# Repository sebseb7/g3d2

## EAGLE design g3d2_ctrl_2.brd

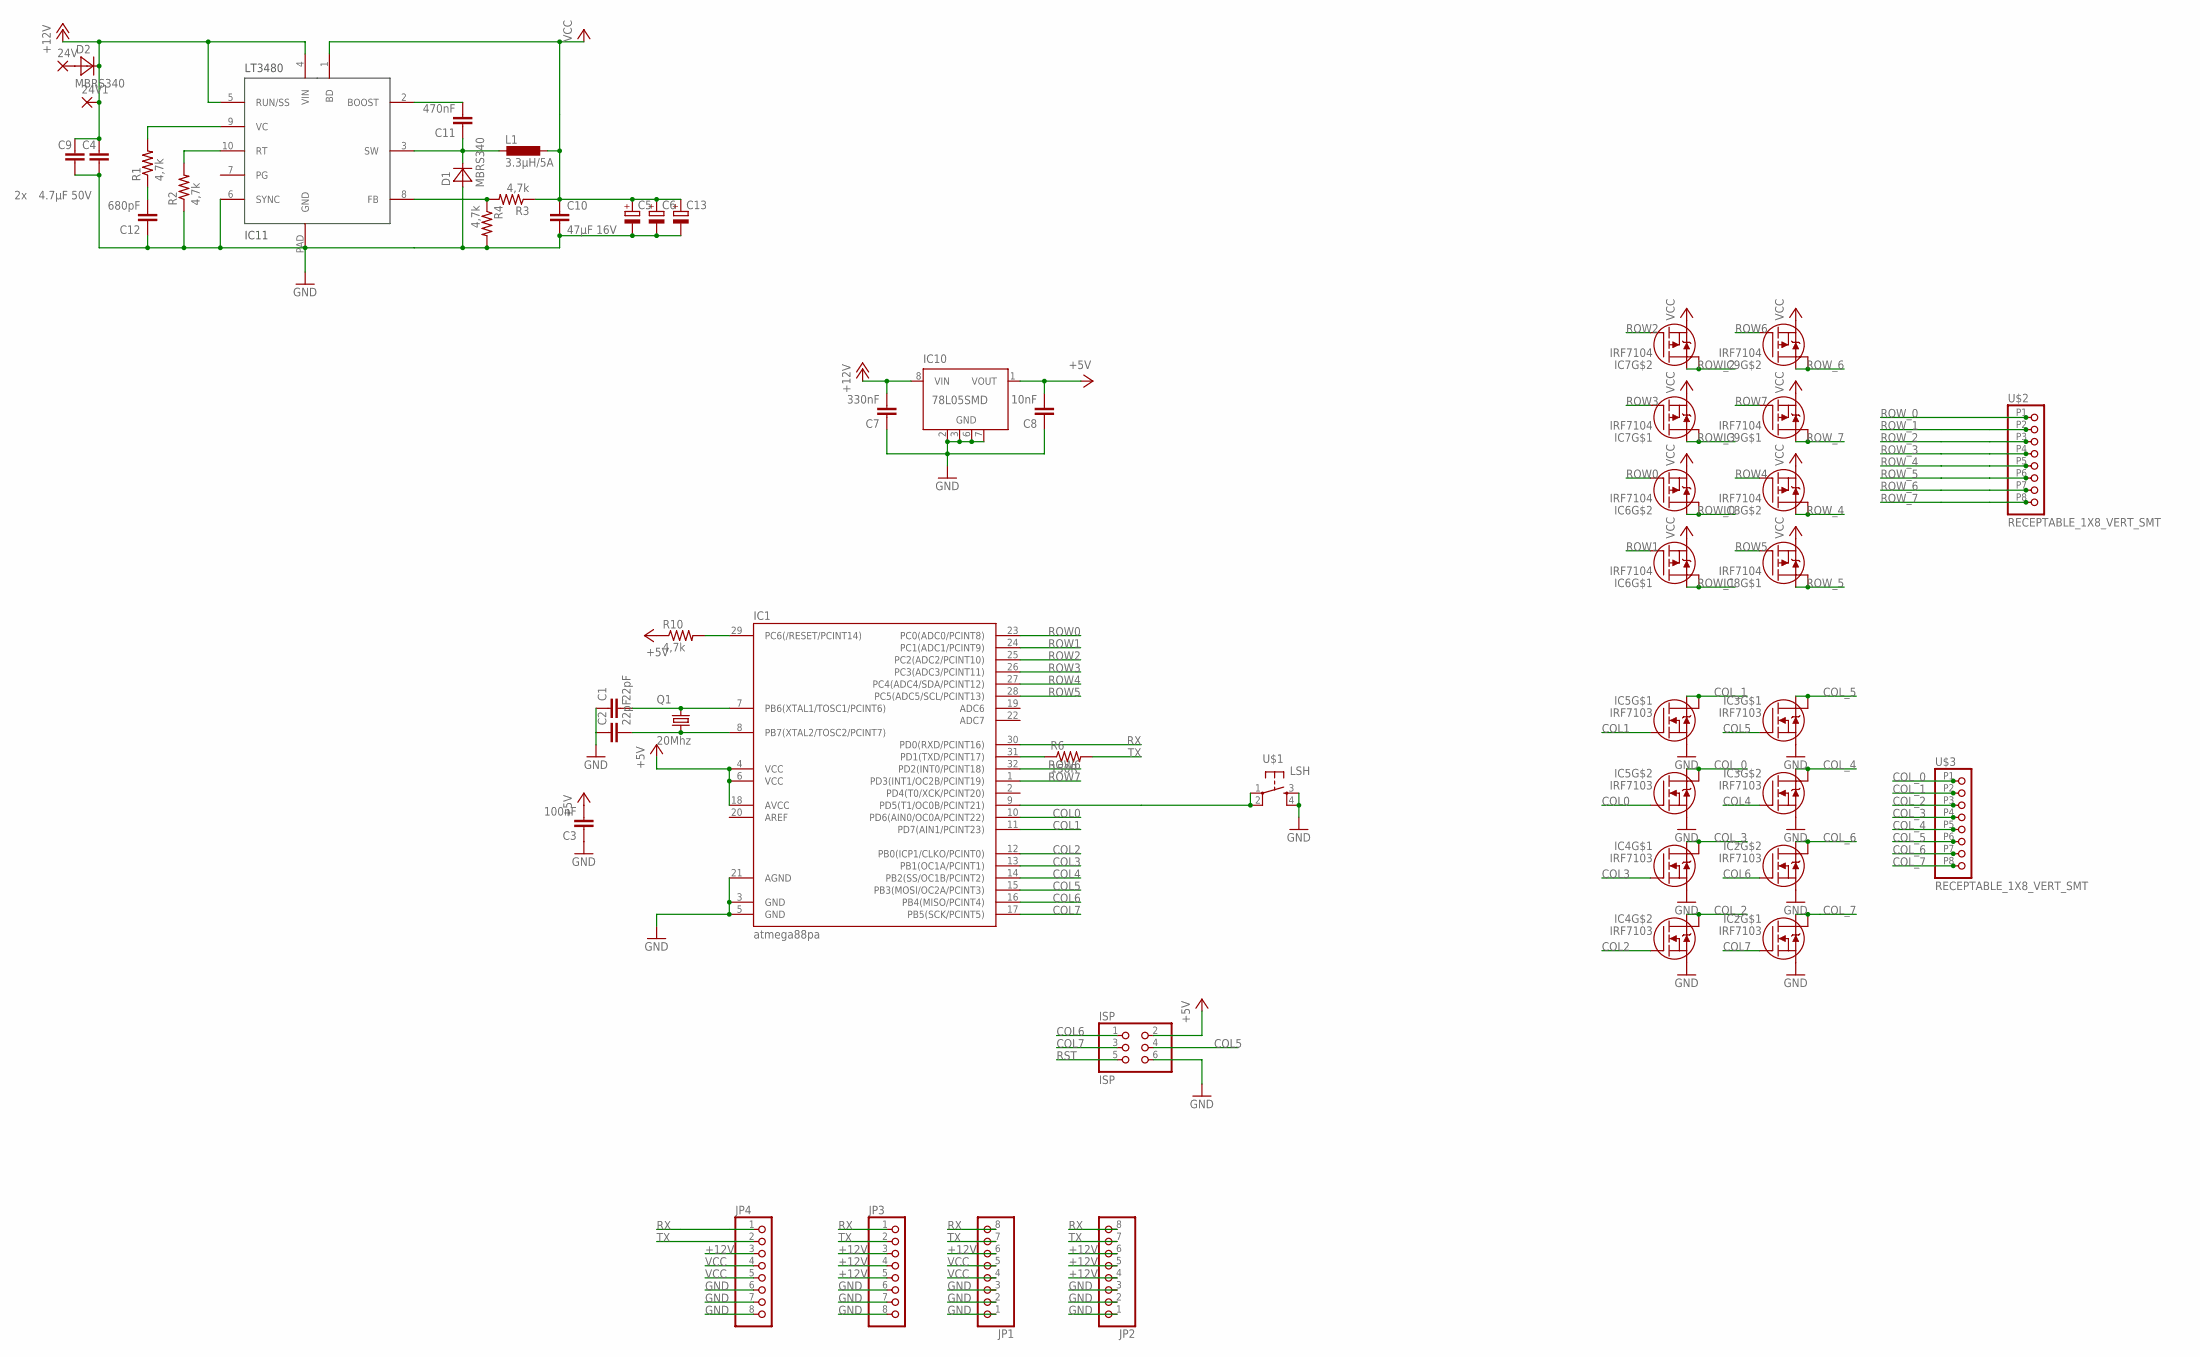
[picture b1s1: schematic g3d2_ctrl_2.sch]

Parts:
24V, 24V1: SMD5; SMD2,54-5,08
C1, C2: 22pF; 0805
C3: 100nF; 0805
C4, C9: 4.7µF 50V; 1210
C5, C6, C13: CPOL-EUSMCD; SMC_D
C7: 330nF; 0805
C8: 10nF; 0805
C10: 47µF 16V; 1210
C11: 470nF; 0805
C12: 680pF; 0805
D1, D2: MBRS340; DO214AB
IC1: atmega88pa; TQFP32-08
IC2, IC3, IC4, IC5: IRF7103; SO8-2
IC6, IC7, IC8, IC9: IRF7104; SO8-2
IC10: 78L05SMD; SO08
IC11: LT3972; MSOP10-PAD
ISP: ISP; 2X03
JP1, JP2, JP3, JP4: PINHD-1X08_2.54-SMD-90°; 1X08SMD/90
L1: 3.3µH/5A; DO3316P
Q1: 20Mhz; X22
R1, R2, R3, R4, R10: 4,7k; 0805
R6: 150R; 0805
U$1: LSH
U$2, U$3: RECEPTABLE_1X8_VERT_SMT

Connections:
+5V: C3.2, C8.2, IC1.4 (VCC), IC1.6 (VCC), IC1.18 (AVCC), IC10.1 (VOUT), ISP.2, R10.1
+12V: 24V1.1, C4.1, C7.2, C9.1, D2.K (C), IC10.8 (VIN), IC11.4 (VIN), IC11.5 (RUN/SS), JP1.6, JP2.4, JP2.5, JP2.6, JP3.3, JP3.4, JP3.5, JP4.3
COL0: IC1.10 (PD6(AIN0/OC0A/PCINT22)), IC5.4 (G)
COL1: IC1.11 (PD7(AIN1/PCINT23)), IC5.2 (G)
COL2: IC1.12 (PB0(ICP1/CLKO/PCINT0)), IC4.4 (G)
COL3: IC1.13 (PB1(OC1A/PCINT1)), IC4.2 (G)
COL4: IC1.14 (PB2(SS/OC1B/PCINT2)), IC3.4 (G)
COL5: IC1.15 (PB3(MOSI/OC2A/PCINT3)), IC3.2 (G), ISP.4
COL6: IC1.16 (PB4(MISO/PCINT4)), IC2.4 (G), ISP.1
COL7: IC1.17 (PB5(SCK/PCINT5)), IC2.2 (G), ISP.3
COL_0: IC5.5 (D), IC5.6 (D), U$3.P1 (1)
COL_1: IC5.7 (D), IC5.8 (D), U$3.P2 (2)
COL_2: IC4.5 (D), IC4.6 (D), U$3.P3 (3)
COL_3: IC4.7 (D), IC4.8 (D), U$3.P4 (4)
COL_4: IC3.5 (D), IC3.6 (D), U$3.P5 (5)
COL_5: IC3.7 (D), IC3.8 (D), U$3.P6 (6)
COL_6: IC2.5 (D), IC2.6 (D), U$3.P7 (7)
COL_7: IC2.7 (D), IC2.8 (D), U$3.P8 (8)
GND: C1.1, C2.1, C3.1, C4.2, C5.-, C6.-, C7.1, C8.1, C9.2, C10.2, C12.1, C13.-, D1.A, IC1.3 (GND), IC1.5 (GND), IC1.21 (AGND), IC2.1 (S), IC2.3 (S), IC3.1 (S), IC3.3 (S), IC4.1 (S), IC4.3 (S), IC5.1 (S), IC5.3 (S), IC10.2 (GND), IC10.3 (GND), IC10.6 (GND), IC10.7 (GND), IC11.6 (SYNC), IC11.PAD (GND), ISP.6, JP1.1, JP1.2, JP1.3, JP2.1, JP2.2, JP2.3, JP3.6, JP3.7, JP3.8, JP4.6, JP4.7, JP4.8, R2.1, R4.2, U$1.3, U$1.4
unnamed: C2.2, IC1.8 (PB7(XTAL2/TOSC2/PCINT7)), Q1.1
unnamed: C1.2, IC1.7 (PB6(XTAL1/TOSC1/PCINT6)), Q1.3 (2)
unnamed: IC1.31 (PD1(TXD/PCINT17)), R6.1
unnamed: 24V.1, D2.A
unnamed: IC11.10 (RT), R2.2
unnamed: IC1.9 (PD5(T1/OC0B/PCINT21)), U$1.1, U$1.2
unnamed: C12.2, R1.1
unnamed: IC11.9 (VC), R1.2
unnamed: C11.1, D1.K (C), IC11.3 (SW), L1.1
unnamed: IC11.8 (FB), R3.2, R4.1
unnamed: C11.2, IC11.2 (BOOST)
ROW0: IC1.23 (PC0(ADC0/PCINT8)), IC6.4 (G)
ROW1: IC1.24 (PC1(ADC1/PCINT9)), IC6.2 (G)
ROW2: IC1.25 (PC2(ADC2/PCINT10)), IC7.4 (G)
ROW3: IC1.26 (PC3(ADC3/PCINT11)), IC7.2 (G)
ROW4: IC1.27 (PC4(ADC4/SDA/PCINT12)), IC8.4 (G)
ROW5: IC1.28 (PC5(ADC5/SCL/PCINT13)), IC8.2 (G)
ROW6: IC1.32 (PD2(INT0/PCINT18)), IC9.4 (G)
ROW7: IC1.1 (PD3(INT1/OC2B/PCINT19)), IC9.2 (G)
ROW_0: IC6.5 (D), IC6.6 (D), U$2.P1 (1)
ROW_1: IC6.7 (D), IC6.8 (D), U$2.P2 (2)
ROW_2: IC7.5 (D), IC7.6 (D), U$2.P3 (3)
ROW_3: IC7.7 (D), IC7.8 (D), U$2.P4 (4)
ROW_4: IC8.5 (D), IC8.6 (D), U$2.P5 (5)
ROW_5: IC8.7 (D), IC8.8 (D), U$2.P6 (6)
ROW_6: IC9.5 (D), IC9.6 (D), U$2.P7 (7)
ROW_7: IC9.7 (D), IC9.8 (D), U$2.P8 (8)
RST: IC1.29 (PC6(/RESET/PCINT14)), ISP.5, R10.2
RX: IC1.30 (PD0(RXD/PCINT16)), JP1.8, JP2.8, JP3.1, JP4.1
TX: JP1.7, JP2.7, JP3.2, JP4.2, R6.2
VCC: C5.+, C6.+, C10.1, C13.+, IC6.1 (S), IC6.3 (S), IC7.1 (S), IC7.3 (S), IC8.1 (S), IC8.3 (S), IC9.1 (S), IC9.3 (S), IC11.1 (BD), JP1.4, JP1.5, JP4.4, JP4.5, L1.2, R3.1

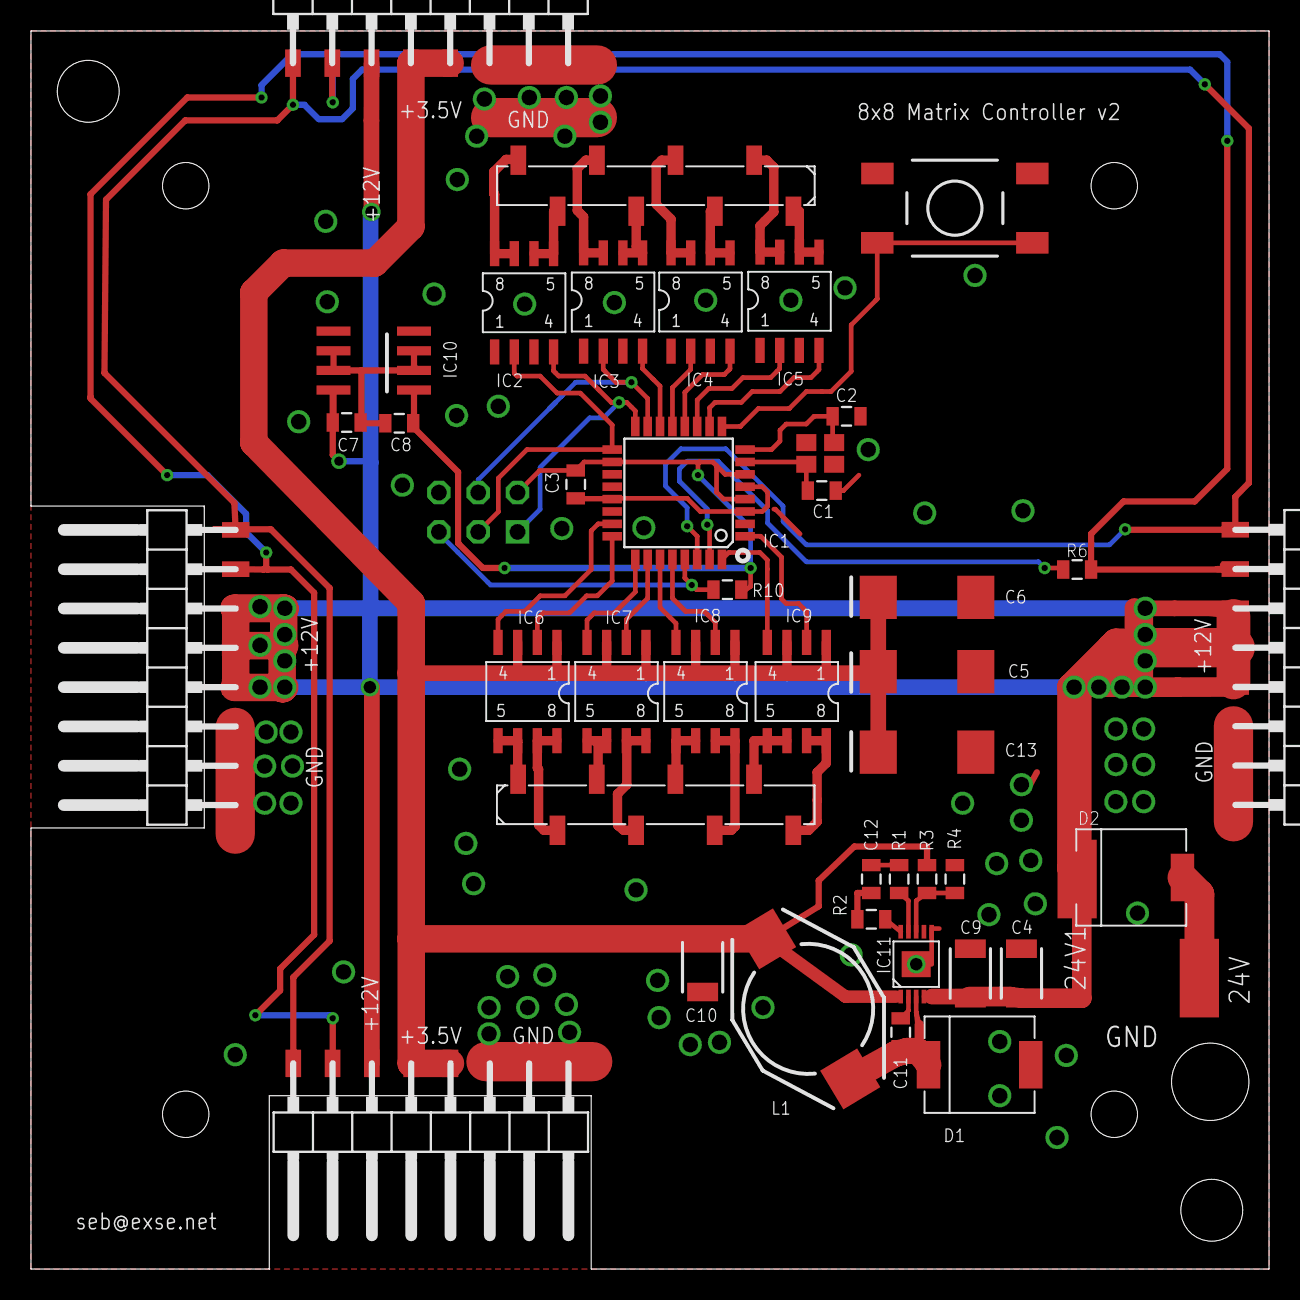
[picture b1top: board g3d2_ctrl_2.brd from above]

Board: 2 copper layers, 80.0 x 80.0 mm, 44 parts (1 on the bottom side), 50 nets.

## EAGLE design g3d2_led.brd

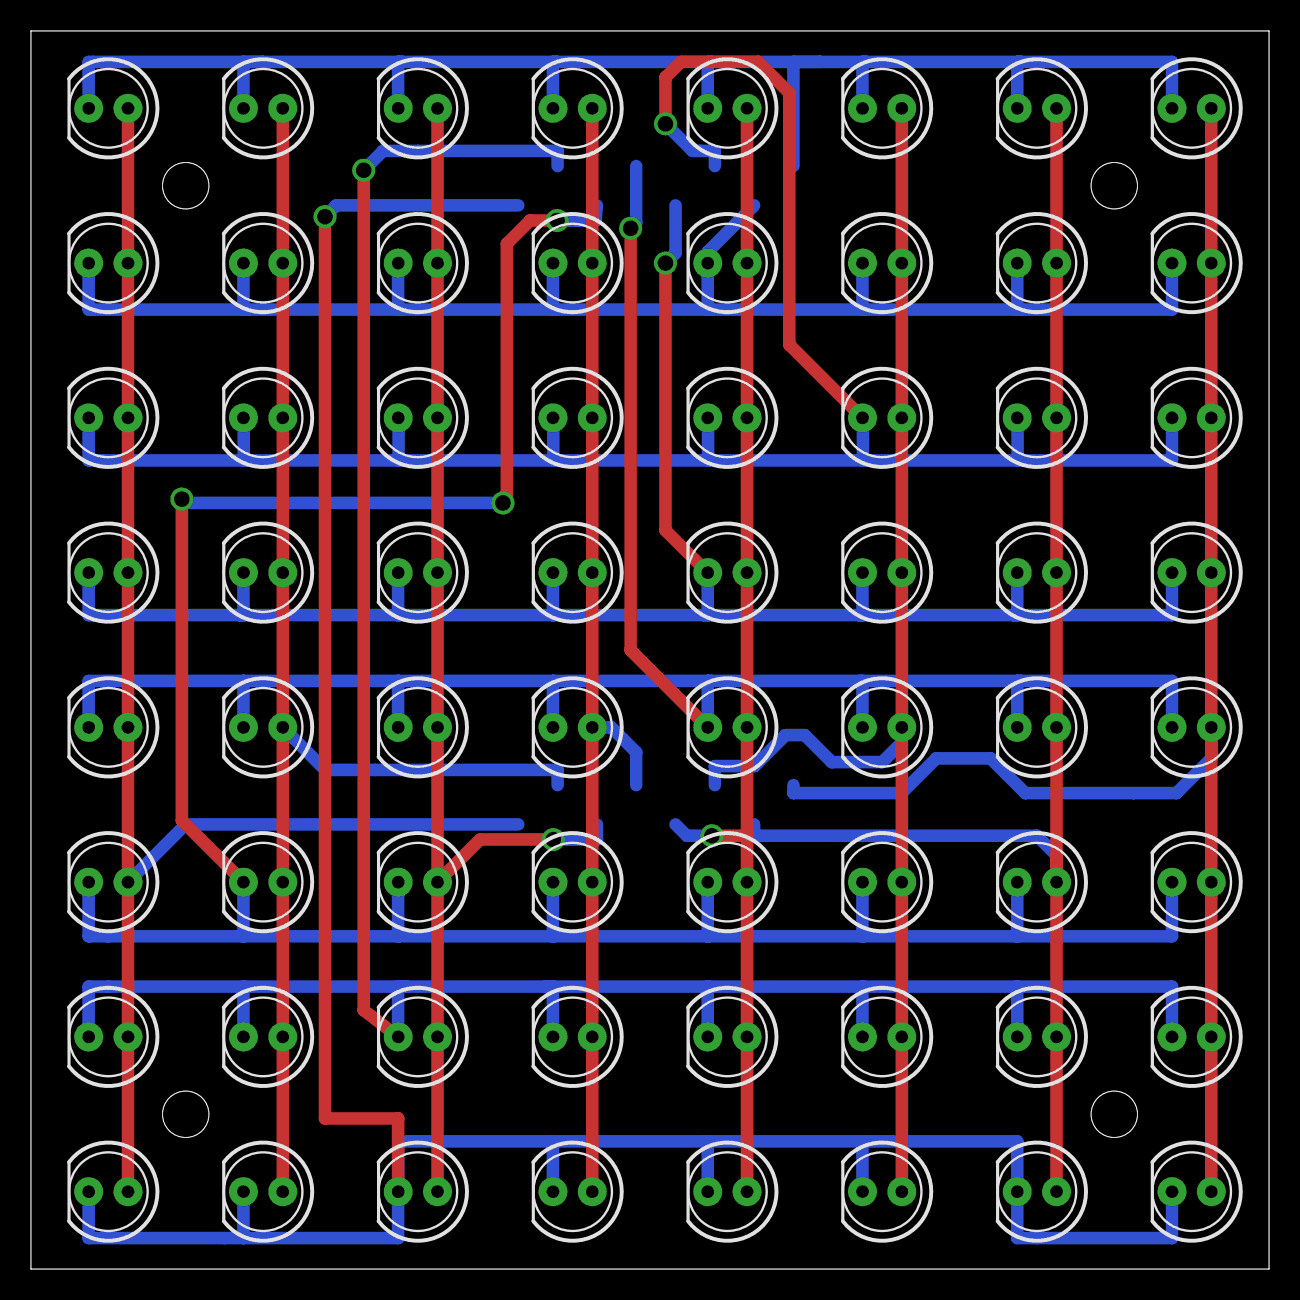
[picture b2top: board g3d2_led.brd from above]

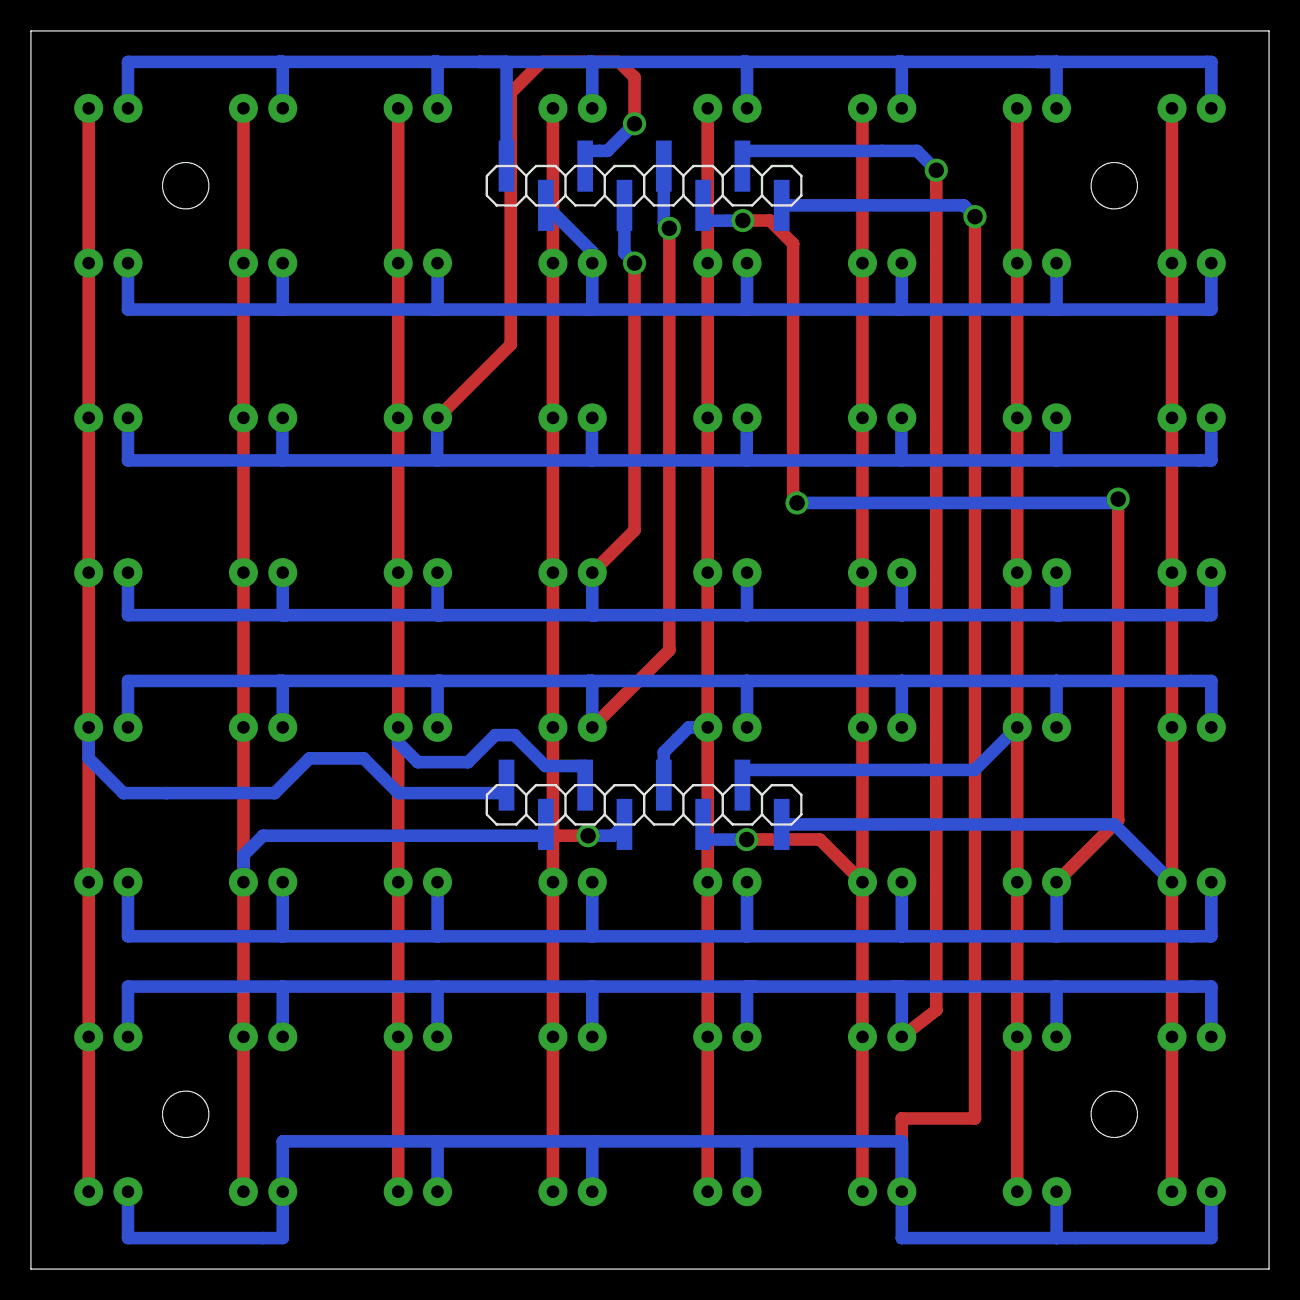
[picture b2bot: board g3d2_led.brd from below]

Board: 2 copper layers, 80.0 x 80.0 mm, 66 parts (2 on the bottom side), 16 nets.

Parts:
JP3, JP4: 1X08SMD
LED1, LED2, LED3, LED4, LED5, LED6, LED7, LED8, LED9, LED10, LED11, LED12, LED13, LED14, LED15, LED16, LED17, LED18, LED19, LED20, LED21, LED22, LED23, LED24, LED25, LED26, LED27, LED28, LED29, LED30, LED31, LED32, LED33, LED34, LED35, LED36, LED37, LED38, LED39, LED40, LED41, LED42, LED43, LED44, LED45, LED46, LED47, LED48, LED49, LED50, LED51, LED52, LED53, LED54, LED55, LED56, LED57, LED58, LED59, LED60, LED61, LED62, LED63, LED64: LED5MM

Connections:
unnamed: JP4.1, LED1.A, LED2.A, LED3.A, LED4.A, LED5.A, LED6.A, LED7.A, LED8.A
unnamed: JP4.2, LED9.A, LED10.A, LED11.A, LED12.A, LED13.A, LED14.A, LED15.A, LED16.A
unnamed: JP4.3, LED17.A, LED18.A, LED19.A, LED20.A, LED21.A, LED22.A, LED23.A, LED24.A
unnamed: JP4.4, LED25.A, LED26.A, LED27.A, LED28.A, LED29.A, LED30.A, LED31.A, LED32.A
unnamed: JP4.5, LED33.A, LED34.A, LED35.A, LED36.A, LED37.A, LED38.A, LED39.A, LED40.A
unnamed: JP4.6, LED41.A, LED42.A, LED43.A, LED44.A, LED45.A, LED46.A, LED47.A, LED48.A
unnamed: JP4.7, LED49.A, LED50.A, LED51.A, LED52.A, LED53.A, LED54.A, LED55.A, LED56.A
unnamed: JP4.8, LED57.A, LED58.A, LED59.A, LED60.A, LED61.A, LED62.A, LED63.A, LED64.A
unnamed: JP3.1, LED1.K, LED9.K, LED17.K, LED25.K, LED33.K, LED41.K, LED49.K, LED57.K
unnamed: JP3.2, LED2.K, LED10.K, LED18.K, LED26.K, LED34.K, LED42.K, LED50.K, LED58.K
unnamed: JP3.3, LED3.K, LED11.K, LED19.K, LED27.K, LED35.K, LED43.K, LED51.K, LED59.K
unnamed: JP3.4, LED4.K, LED12.K, LED20.K, LED28.K, LED36.K, LED44.K, LED52.K, LED60.K
unnamed: JP3.5, LED5.K, LED13.K, LED21.K, LED29.K, LED37.K, LED45.K, LED53.K, LED61.K
unnamed: JP3.6, LED6.K, LED14.K, LED22.K, LED30.K, LED38.K, LED46.K, LED54.K, LED62.K
unnamed: JP3.7, LED7.K, LED15.K, LED23.K, LED31.K, LED39.K, LED47.K, LED55.K, LED63.K
unnamed: JP3.8, LED8.K, LED16.K, LED24.K, LED32.K, LED40.K, LED48.K, LED56.K, LED64.K

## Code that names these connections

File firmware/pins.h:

#ifndef _PINS_H
#define _PINS_H


#define COL0_PORT PORTD
#define COL1_PORT PORTD
#define COL2_PORT PORTB
#define COL3_PORT PORTB
#define COL4_PORT PORTB
#define COL5_PORT PORTB
#define COL6_PORT PORTB
#define COL7_PORT PORTB

#define ROW0_PORT PORTC
#define ROW1_PORT PORTC
#define ROW2_PORT PORTC
#define ROW3_PORT PORTC
#define ROW4_PORT PORTC
#define ROW5_PORT PORTC
#define ROW6_PORT PORTD
#define ROW7_PORT PORTD

#define COL0_DDR DDRD
#define COL1_DDR DDRD
#define COL2_DDR DDRB
#define COL3_DDR DDRB
#define COL4_DDR DDRB
#define COL5_DDR DDRB
#define COL6_DDR DDRB
#define COL7_DDR DDRB

#define ROW0_DDR DDRC
#define ROW1_DDR DDRC
#define ROW2_DDR DDRC
#define ROW3_DDR DDRC
#define ROW4_DDR DDRC
#define ROW5_DDR DDRC
#define ROW6_DDR DDRD
#define ROW7_DDR DDRD

#define COL0_PIN PIND6
#define COL1_PIN PIND7
#define COL2_PIN PINB0
#define COL3_PIN PINB1
#define COL4_PIN PINB2
#define COL5_PIN PINB3
#define COL6_PIN PINB4
#define COL7_PIN PINB5

#define ROW0_PIN PINC0
#define ROW1_PIN PINC1
#define ROW2_PIN PINC2
#define ROW3_PIN PINC3
#define ROW4_PIN PINC4
#define ROW5_PIN PINC5
#define ROW6_PIN PIND2
#define ROW7_PIN PIND3

#define ROW0_OFF ROW0_PORT |= (1<<ROW0_PIN)
#define ROW1_OFF ROW1_PORT |= (1<<ROW1_PIN)
#define ROW2_OFF ROW2_PORT |= (1<<ROW2_PIN)
#define ROW3_OFF ROW3_PORT |= (1<<ROW3_PIN)
#define ROW4_OFF ROW4_PORT |= (1<<ROW4_PIN)
#define ROW5_OFF ROW5_PORT |= (1<<ROW5_PIN)
#define ROW6_OFF ROW6_PORT |= (1<<ROW6_PIN)
#define ROW7_OFF ROW7_PORT |= (1<<ROW7_PIN)

#define ROW0_ON ROW0_PORT &= ~(1<<ROW0_PIN)
#define ROW1_ON ROW1_PORT &= ~(1<<ROW1_PIN)
#define ROW2_ON ROW2_PORT &= ~(1<<ROW2_PIN)
#define ROW3_ON ROW3_PORT &= ~(1<<ROW3_PIN)
#define ROW4_ON ROW4_PORT &= ~(1<<ROW4_PIN)
#define ROW5_ON ROW5_PORT &= ~(1<<ROW5_PIN)
#define ROW6_ON ROW6_PORT &= ~(1<<ROW6_PIN)
#define ROW7_ON ROW7_PORT &= ~(1<<ROW7_PIN)

#define COL0_ON COL0_PORT |= (1<<COL0_PIN)
#define COL1_ON COL1_PORT |= (1<<COL1_PIN)
#define COL2_ON COL2_PORT |= (1<<COL2_PIN)
#define COL3_ON COL3_PORT |= (1<<COL3_PIN)
#define COL4_ON COL4_PORT |= (1<<COL4_PIN)
#define COL5_ON COL5_PORT |= (1<<COL5_PIN)
#define COL6_ON COL6_PORT |= (1<<COL6_PIN)
#define COL7_ON COL7_PORT |= (1<<COL7_PIN)

#define COL0_OFF COL0_PORT &= ~(1<<COL0_PIN)
#define COL1_OFF COL1_PORT &= ~(1<<COL1_PIN)
#define COL2_OFF COL2_PORT &= ~(1<<COL2_PIN)
#define COL3_OFF COL3_PORT &= ~(1<<COL3_PIN)
#define COL4_OFF COL4_PORT &= ~(1<<COL4_PIN)
#define COL5_OFF COL5_PORT &= ~(1<<COL5_PIN)
#define COL6_OFF COL6_PORT &= ~(1<<COL6_PIN)
#define COL7_OFF COL7_PORT &= ~(1<<COL7_PIN)


#endif

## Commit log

2011-10-28 initial
2011-10-28 2nd image
2011-11-04 moved to here
2011-11-04 new images
2011-11-04 another image added
2011-11-04 values added
2011-11-17 fixed collision
2011-11-17 fixed tnames fontsize
2011-11-17 fixed a few clearance problems
2011-11-20 initial test version (barebone) of g3d2 master firmware
2011-11-20 now binaries depend on the makefile
2011-11-20 small fixes
2011-11-20 -O0 > -O1 (binary nearly 50% smaller)
2011-11-20 added wildcards for .c and .s
2011-11-20 removed stuff
2011-11-21 moved path to bash_profile
2011-11-21 fixed line-breaks , added uart driver
2011-11-21 osx fix
2011-11-21 gitignore
2011-11-21 added some values
2011-11-21 case
2011-11-21 newer lpc headers, removed unnessesary stuff, got uart working, got sprintf working
2011-11-21 changed string
2011-11-21 smaller sprintf
2011-11-21 added comment
2011-11-21 implemented delay with systick
2011-11-21 small edits
2011-11-30 initial bootloader for g3d2
2011-11-30 led test
2011-11-30 cmsis 2.0 -> 2.1
2011-12-02 initial test firmware
2011-12-02 uart activated
2011-12-02 nearly final
2011-12-02 checkpoint
2011-12-02 new interrupt architecture
2011-12-02 removed second buffer
2011-12-02 full frame done
2011-12-02 perl plasma
2011-12-02 set pixel
2011-12-02 removed
2011-12-02 strobe
2011-12-02 4 bit
2011-12-02 2 modules working
2011-12-03 3 modules up, reduced brightness
2011-12-03 cleanup
2011-12-03 values beautified
2011-12-05 initial version with display
2011-12-05 fixed diode
2011-12-05 next step towards version2
2011-12-05 v2 nearly done
2011-12-06 v2 done
2011-12-06 final version for production
2011-12-06 beautify & some values
2011-12-07 values
2011-12-10 addr in makefile
2011-12-15 frame sync
2011-12-15 more fixes
2011-12-15 font-script
2011-12-15 all number
2011-12-15 big X
2011-12-16 makefile not executable
2011-12-17 boot-sequence & addr display on boot
2011-12-17 new escaping
2011-12-17 full frame via single pixel
2011-12-17 addr display
2011-12-17 local tetris, for operation without lpc1768 board
2011-12-17 small demo to detect bad pixels
2011-12-17 multithreaded
2011-12-17 small fix
2011-12-19 new version
2011-12-19 addr stay on
2011-12-19 replaced diode with resistor
2011-12-19 g3s2 - new type of g3d2 simulator
2011-12-19 image
2011-12-20 small change
2011-12-20 cpu consumption improovements
2011-12-20 added memcpy
2011-12-20 added pixelfonts mdoule
2011-12-20 check these options
2011-12-20 no longer necessary
2011-12-20 use buttons for testing
2011-12-20 symlinks to the game-files
2011-12-20 .gitignore
2011-12-20 updated submodule
2011-12-22 test
2011-12-24 r0ket logger
2011-12-25 new arm module
2011-12-25 some changes and nrf testcode
2011-12-25 nrf24l01 tests
2011-12-26 build fix
2011-12-26 plasma2
2012-01-08 default values & completion hints
2012-01-08 deleted
2012-01-08 splitted files
2012-01-08 tab fixes
2012-01-08 make signal stength configurable
2012-01-08 space2tab
2012-02-03 fixed
2012-02-04 g3d2 wallServer
2012-02-04 device fix and formula
2012-02-04 misc
2012-02-14 perl tcp examples for g3d2
2012-02-14 ftdi name update
2012-02-14 small optimizations
2012-02-14 optimize
2012-02-14 ipv6
2012-02-15 removed warns
2012-02-15 flowcontrol
2012-03-09 server update
2012-03-11 small optimization
2012-03-11 reenable bulk update
2012-03-11 cpu consumtion reduction by chaning the pixel order in full frame
2012-03-15 canges
2012-03-15 various updates
2012-03-31 recordings
2012-03-31 readded delay
2012-04-02 added rainboardroad animation
2012-04-06 change coodinates & single pixel protocol
2012-04-06 start couting at 1
2012-04-09 p o p
2012-04-09 nyan
2012-04-09 rick
2012-04-10 random
2012-04-10 reduced start delay
2012-07-31 flowctrl
2012-09-12 routing gap fix
2012-11-13 production ready
2012-11-19 fixed g3s2
